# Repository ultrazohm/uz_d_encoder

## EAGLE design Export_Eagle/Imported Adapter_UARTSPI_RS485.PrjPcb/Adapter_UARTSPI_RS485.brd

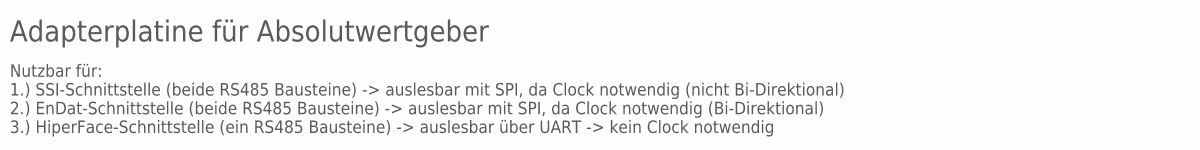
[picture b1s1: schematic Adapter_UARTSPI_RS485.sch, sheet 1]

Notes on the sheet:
Adapterplatine für Absolutwertgeber
Nutzbar für: 1.) SSI-Schnittstelle (beide RS485 Bausteine) -> auslesbar mit SPI, da Clock notwendig (nicht Bi-Direktional) 2.) EnDat-Schnittstelle (beide RS485 Bausteine) -> auslesbar mit SPI, da Clock notwendig (Bi-Direktional) 3.) HiperFace-Schnittstelle (ein RS485 Bausteine) -> auslesbar über UA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

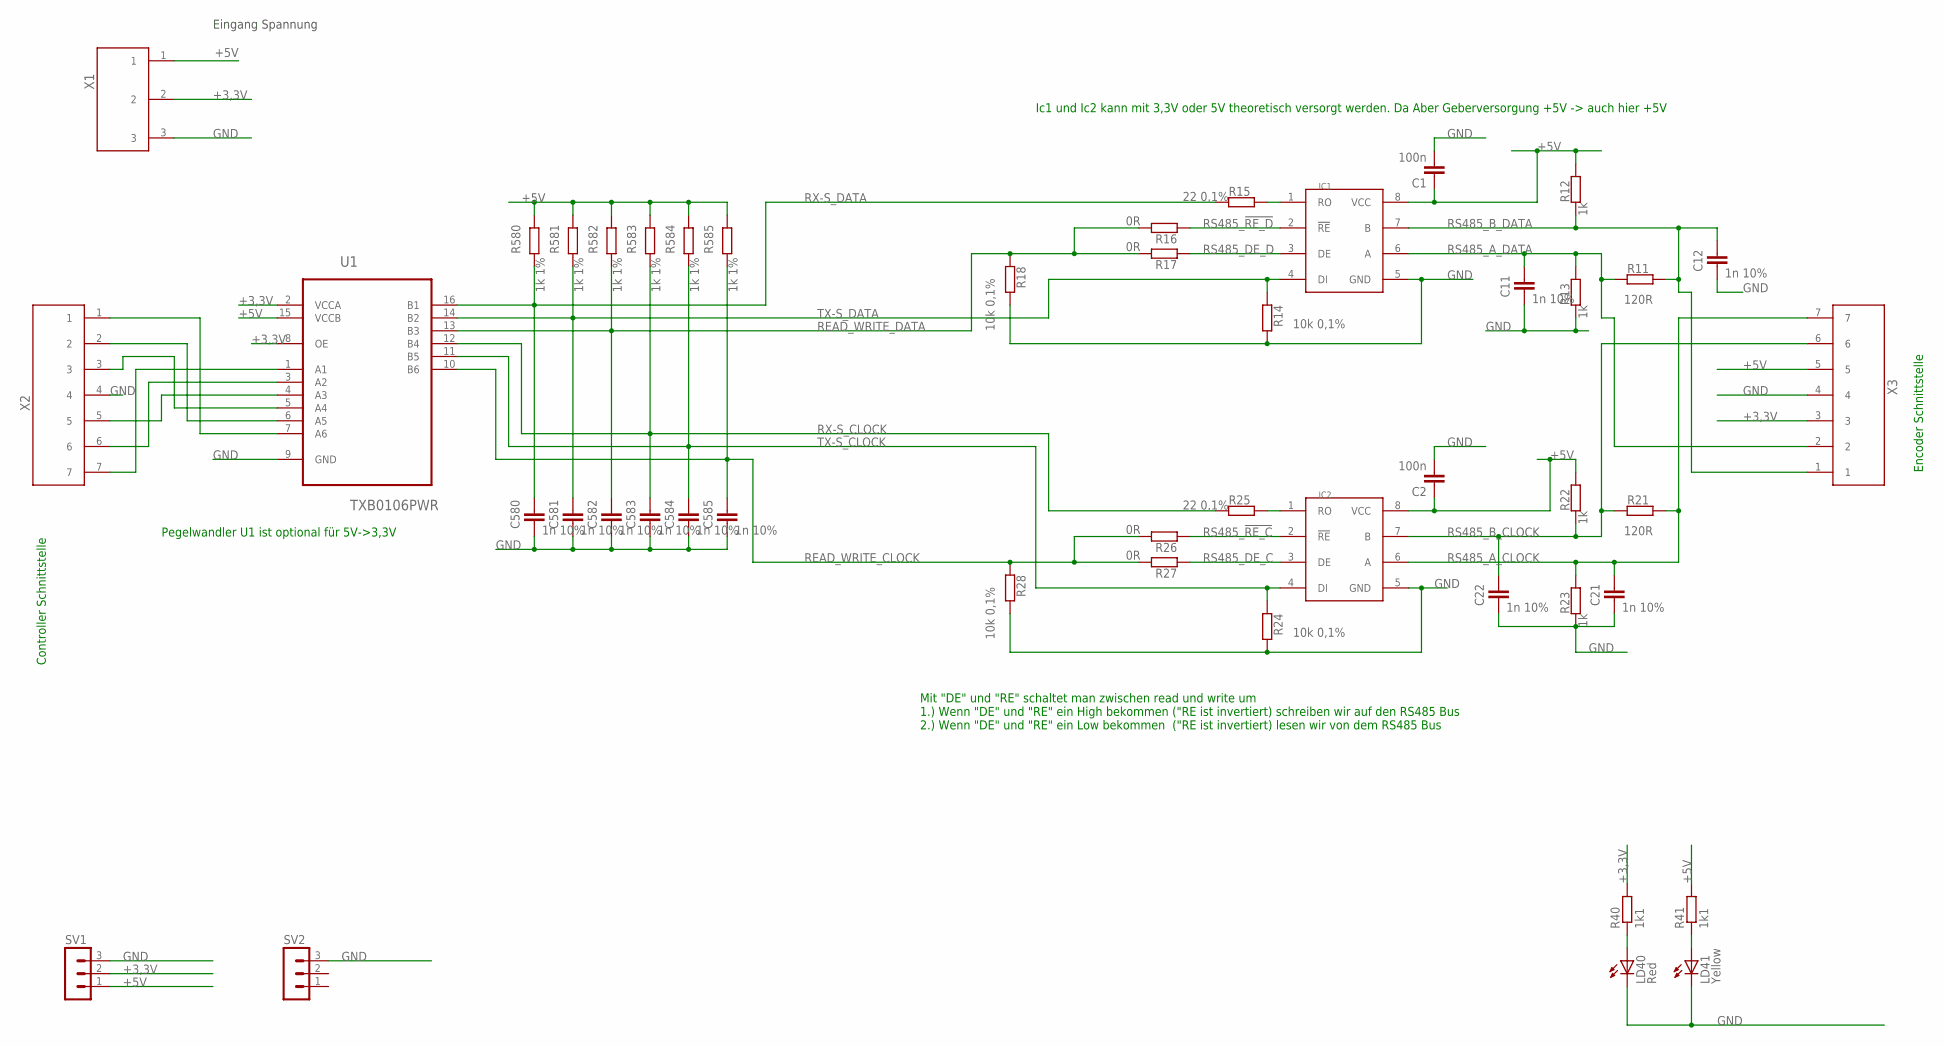
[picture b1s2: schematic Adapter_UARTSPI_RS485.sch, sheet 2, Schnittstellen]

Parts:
C1, C2: 100n; SMD-0603
C11, C12, C21, C22, C580, C581, C582, C583, C584, C585: 1n 10%; SMD-0603
IC1, IC2: RS485-MAXIM; SOIC8
LD40: Red; CHIP-LED0805
LD41: Yellow; CHIP-LED0805
R11, R21: 120R; R0603
R12, R13, R22, R23: 1k; R0603
R14, R18, R24, R28: 10k 0,1%; R0603
R15, R25: 22 0,1%; R0603
R16, R17, R26, R27: 0R; R0603
R40, R41: 1k1; R0805
R580, R581, R582, R583, R584, R585: 1k 1%; R0603
SV1, SV2: MA03-1
U1: TXB0106PWR; SOP65P640X120-16N
X1: KLEMME_3POLIG_2,54
X2, X3: KLEMME_7POLIG_2,54

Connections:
+3,3V: R40.2, SV1.2, U1.2 (VCCA), U1.8 (OE), X1.2, X3.3
+5V: C1.1, C2.1, IC1.8 (VCC), IC2.8 (VCC), R12.1, R22.1, R41.2, R580.2, R581.2, R582.2, R583.2, R584.2, R585.2, SV1.1, U1.15 (VCCB), X1.1, X3.5
GND: C1.2, C2.2, C11.2, C12.2, C21.2, C22.2, C580.2, C581.2, C582.2, C583.2, C584.2, C585.2, IC1.5 (GND), IC2.5 (GND), LD40.C, LD41.C, R13.2, R14.1, R18.1, R23.2, R24.1, R28.1, SV1.3, SV2.3, U1.9 (GND), X1.3, X2.4, X3.4
unnamed: IC2.1 (RO), R25.1
unnamed: LD41.A, R41.1
unnamed: LD40.A, R40.1
unnamed: IC1.1 (RO), R15.1
R/W_CLOCK: U1.7 (A6), X2.1
R/W_DATA: U1.4 (A3), X2.5
READ_WRITE_CLOCK: C585.1, R26.1, R27.1, R28.2, R585.1, U1.10 (B6)
READ_WRITE_DATA: C582.1, R16.1, R17.1, R18.2, R582.1, U1.13 (B3)
RS485_!RE_C: IC2.2 (!RE), R26.2
RS485_!RE_D: IC1.2 (!RE), R16.2
RS485_A_CLOCK: C21.1, IC2.6 (A), R21.1, R23.1, X3.7
RS485_A_DATA: C11.1, IC1.6 (A), R11.2, R13.1, X3.2
RS485_B_CLOCK: C22.1, IC2.7 (B), R21.2, R22.2, X3.6
RS485_B_DATA: C12.1, IC1.7 (B), R11.1, R12.2, X3.1
RS485_DE_C: IC2.3 (DE), R27.2
RS485_DE_D: IC1.3 (DE), R17.2
RX-S_CLOCK: C583.1, R25.2, R583.1, U1.12 (B4)
RX-S_DATA: C580.1, R15.2, R580.1, U1.16 (B1)
RX_CLOCK: U1.5 (A4), X2.3
RX_DATA: U1.1 (A1), X2.7
TX-S_CLOCK: C584.1, IC2.4 (DI), R24.2, R584.1, U1.11 (B5)
TX-S_DATA: C581.1, IC1.4 (DI), R14.2, R581.1, U1.14 (B2)
TX_CLOCK: U1.6 (A5), X2.2
TX_DATA: U1.3 (A2), X2.6

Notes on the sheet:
Eingang Spannung
Pegelwandler U1 ist optional für 5V->3,3V
Mit "DE" und "RE" schaltet man zwischen read und write um 1.) Wenn "DE" und "RE" ein High bekommen ("RE ist invertiert) schreiben wir auf den RS485 Bus 2.) Wenn "DE" und "RE" ein Low bekommen ("RE ist invertiert) lesen wir von dem RS485 Bus
Encoder Schnittstelle
Controller Schnittstelle
Ic1 und Ic2 kann mit 3,3V oder 5V theoretisch versorgt werden. Da Aber Geberversorgung +5V -> auch hier +5V

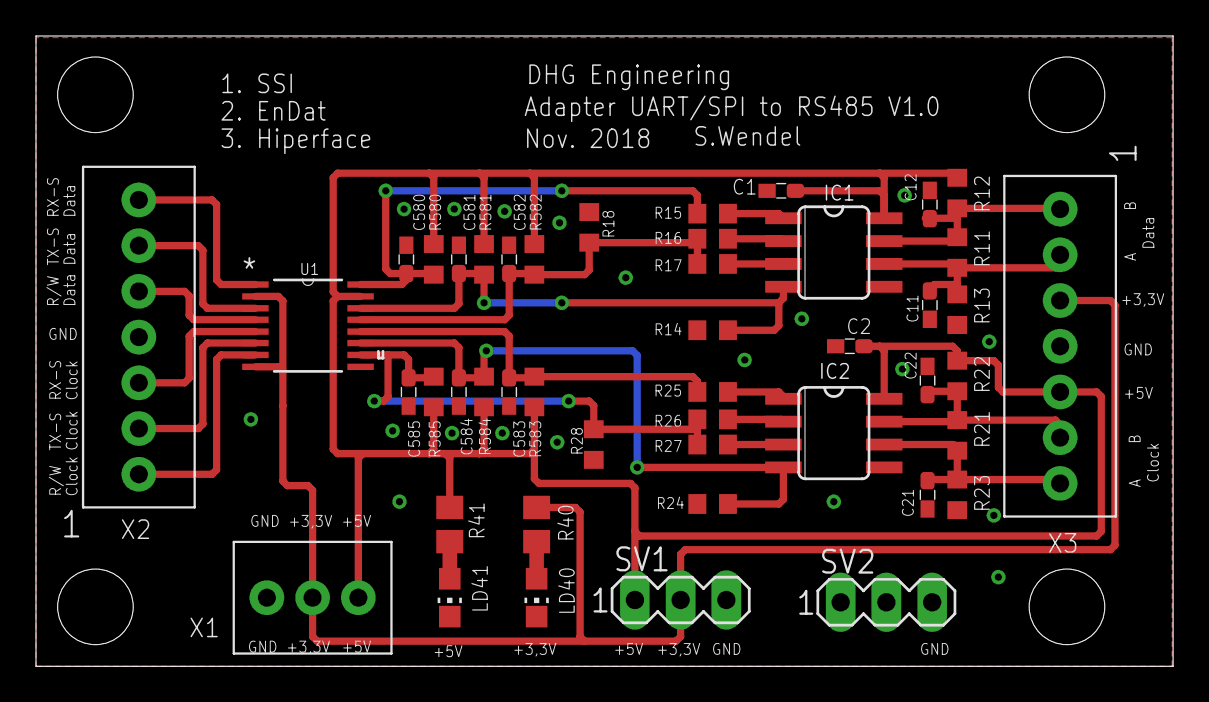
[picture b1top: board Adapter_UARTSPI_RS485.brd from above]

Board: 4 copper layers, 63.2 x 35.0 mm, 46 parts (0 on the bottom side), 27 nets.

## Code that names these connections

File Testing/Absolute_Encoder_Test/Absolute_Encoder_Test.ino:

/*******************************************************************************
 * Test routines for Absolute Encoder Kuebler 8.5863.1234.G721
 *
 * Thomas Effenberger, 2020
 * 
 ******************************************************************************/


//define control pins
#define RX_DATA       7
#define TX_DATA       8
#define RW_DATA       11

#define RX_CLOCK      9
#define TX_CLOCK      10
#define RW_CLOCK      12


// Encoder Definitions



void setup()
{
    //configure Pins
    pinMode(TX_DATA, OUTPUT);
    pinMode(RW_DATA, OUTPUT);
    pinMode(TX_CLOCK, OUTPUT);
    pinMode(RW_CLOCK, OUTPUT);
    
    //digitalWrite(RW_DATA, 1);
    //digitalWrite(RW_CLOCK, 0);
    
    // Start Serial Communication
    Serial.begin(9600);
    
    /*Serial1.setTX(TX_DATA);
    Serial1.setRX(RX_DATA);
    Serial1.transmitterEnable(RW_DATA);
    Serial1.begin(1000000);*/
    
    Serial2.transmitterEnable(RW_CLOCK);
    Serial2.begin(100000);

    Serial3.transmitterEnable(RW_DATA);
    Serial3.begin(100000);
    
}

/** Returns 16bit analog data from LTC231116
 * Automatically wakes device if in nap or sleep mode
 */


void loop()
{

    //Serial2.write(0xAA);
    Serial3.write(0x55);
    //delayMicroseconds(10);
    //Serial2.write(0x55);
    //Serial3.write(0x55);
    
    delayMicroseconds(10);
    
    if (Serial2.available())
    {
        Serial.println(String(Serial2.read()));
    }
    
//    digitalWrite(TX_DATA, 1);
//    digitalWrite(RW_DATA, 1);
//    delayMicroseconds(1);
//    digitalWrite(RW_DATA, 0);
//    delayMicroseconds(1);
    

    
    delay(100);
}

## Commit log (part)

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2020-08-25 Initial version of the sensor board from Esteban and Sebastian
2020-10-16 First Commit Rework Thomas Effenberger
    Datasheets added
    Part numbers added
    Minor schematic changes
    ERC and DRC Errors sovled
    PCB optimized
2020-10-16 Project file updated to last commit
2020-10-16 Issues #3, #4, #12 solved
2020-10-16 Issues #6, #11 solved
2020-10-19 Issues #5, #7 solved
2020-10-19 Issues #2, #17 solved
2020-10-19 Issue #14 solved
2020-10-21 Issues #8, #15, #16 solved
    - Every module has its own IO pins now
    - Debug headers for every IO pin
2020-10-21 Issue #10 solved
2020-10-22 Issues #1, #13, #19 solved
2020-10-22 Issue #20 solved
2020-10-23 Issues #21, #23, #25 solved
2020-10-23 Issues #24, #26 solved
2020-10-23 Issue #28 solved
2020-10-23 Issue #31 solved
2020-10-23 Issue #33 solved
2020-10-23 ordered PCB version
2020-10-26 added missing libraries
2020-10-26 Issue #36 solved
2020-10-26 Componentes Update
2020-10-26 Componentes Update 2
2020-10-26 BOM connected
2020-10-26 More suppliers added
2020-10-26 Issue #38 solved
2020-10-26 BOM Cleanup
2020-10-27 Mechanical Layer Cleanup
2020-10-27 Issue #35 solved, Layer Cleanup
    Minor Layout changes around some 0603 parts due to unifying footprints
2020-10-28 Double Side Layers Added
2020-10-29 Issues #37, #40 solved
2020-11-05 Digital Interfaces bugs removed
    R98-R103 marked as DNP
    "DNP" option resistors values changed to 0R
2020-11-12 Changed ADC Buffer Bypass Resistors to Optional Placement
2020-11-13 Testing Resources and Results added
2020-11-18 ADC Test results and code added
2020-11-27 reference design UART SPI RS485
2020-11-27 Absolute Encoder Tests added
    Absolute Encoder Testcode created
    Datasheets added
    Placement option for logic lines pullups added
2020-12-22 ADC Capacitors moved to TOP
2021-01-14 Issue #42 solved
    Renamed "Digital HALL" to "Incremental Encoder"
2021-01-22 pdfs
2021-02-01 Issue #45 solved
    Digital IO Pins are now zero-based
2021-05-20 Removed University Logos
2021-06-10 Issue #49 solved
    UltraZohm symbols added
2021-06-10 PCB Project updated
2021-06-24 added pinout table for carrier board interface cleaned up absolute encoder schematic
2021-07-13 IP-Core created
2021-07-13 fixed vivado project
2021-07-13 test run
2021-07-23 IP-Core AXI Update
2021-07-30 AXI Port Interface finished, IP Core Documentation updated
2021-10-20 Added resolver VHDL test block with ZedBoard IO connections
2021-10-28 Added issue table + interface
2021-10-28 updated pinout table prepared schematics
2021-11-04 Added resolver IP-core state diagram
2021-11-08 most of the hardware changes (schematic) finished, i2c port expander missing
2021-11-08 schematics completed
2021-11-17 schematics update after review
2021-11-28 alles platziert
2021-11-29 routingv0.1
2021-11-29 layout 0.2
2021-11-30 v0.1 (99unrouted nets left)
2021-11-30 v0.1 (86 traces unrouted, cleaned up others)
2021-11-30 v0.1 20nets unrouted
2021-11-30 routing v1 finished
2021-11-30 First Commit of Felix Kaiser, in IP Core/Resolver there is an updated Vivado Project currently used for debugging on Zedboard; in IP Core/Vitis_ZedboardAXI_Encoder there is a debugging vitis project
2021-12-01 prep'd for changing schematic
2021-12-01 Adapted incremental schem - made it more readable
2021-12-01 incr enc spacing 1mm
2021-12-02 all designators sorted and placed - all layout schematic requests til now finished
2021-12-04 Read data works with Reset of Go bit in Main.C
2021-12-04 All uz_encoderIP.c functions tested open loop via main function
2021-12-08 Unimportant Commit before Checkout to jKlein branch for Altium Project
2021-12-08 hardwareänderungen eingebaut
2021-12-09 added LOS und DOT to Portexpander to have this signal available
2021-12-14 updated project naming and readded thermals
2021-12-19 several small tweaks on layout and schematic basically added ser num field changed pull up for cvn signal to 3v3 instead of 5v referred dvdd of resolver to 5v fused instead of analog supply (filtered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
2021-12-21 A2D Serial Interface working: Reading Data, Reading/Writing Registers; Changes in VHDL and Vitis Project
2021-12-21 Hardware Trigger + dataout Implemented: Max sampling_f = 400kS/s
2021-12-22 all changes implemented
2021-12-23 generated output files for Rev02 folder clean up
2022-01-05 Added High Level Functions to Zedboard Project + cleaned up code
2022-01-11 Higher level functions implemented and tested, switching between Config and Data Mode working
2022-04-04 finished hardware
2022-04-19 small adaptions (rounded edges, quarz traces vias tented)
2022-06-11 commit to switch branches. only altium autosve
